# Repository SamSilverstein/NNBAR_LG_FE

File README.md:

# nnbar-calo-prototype

Readout electronics for NNBAR calorimeter prototype at SU
# NNBAR_LG_FE

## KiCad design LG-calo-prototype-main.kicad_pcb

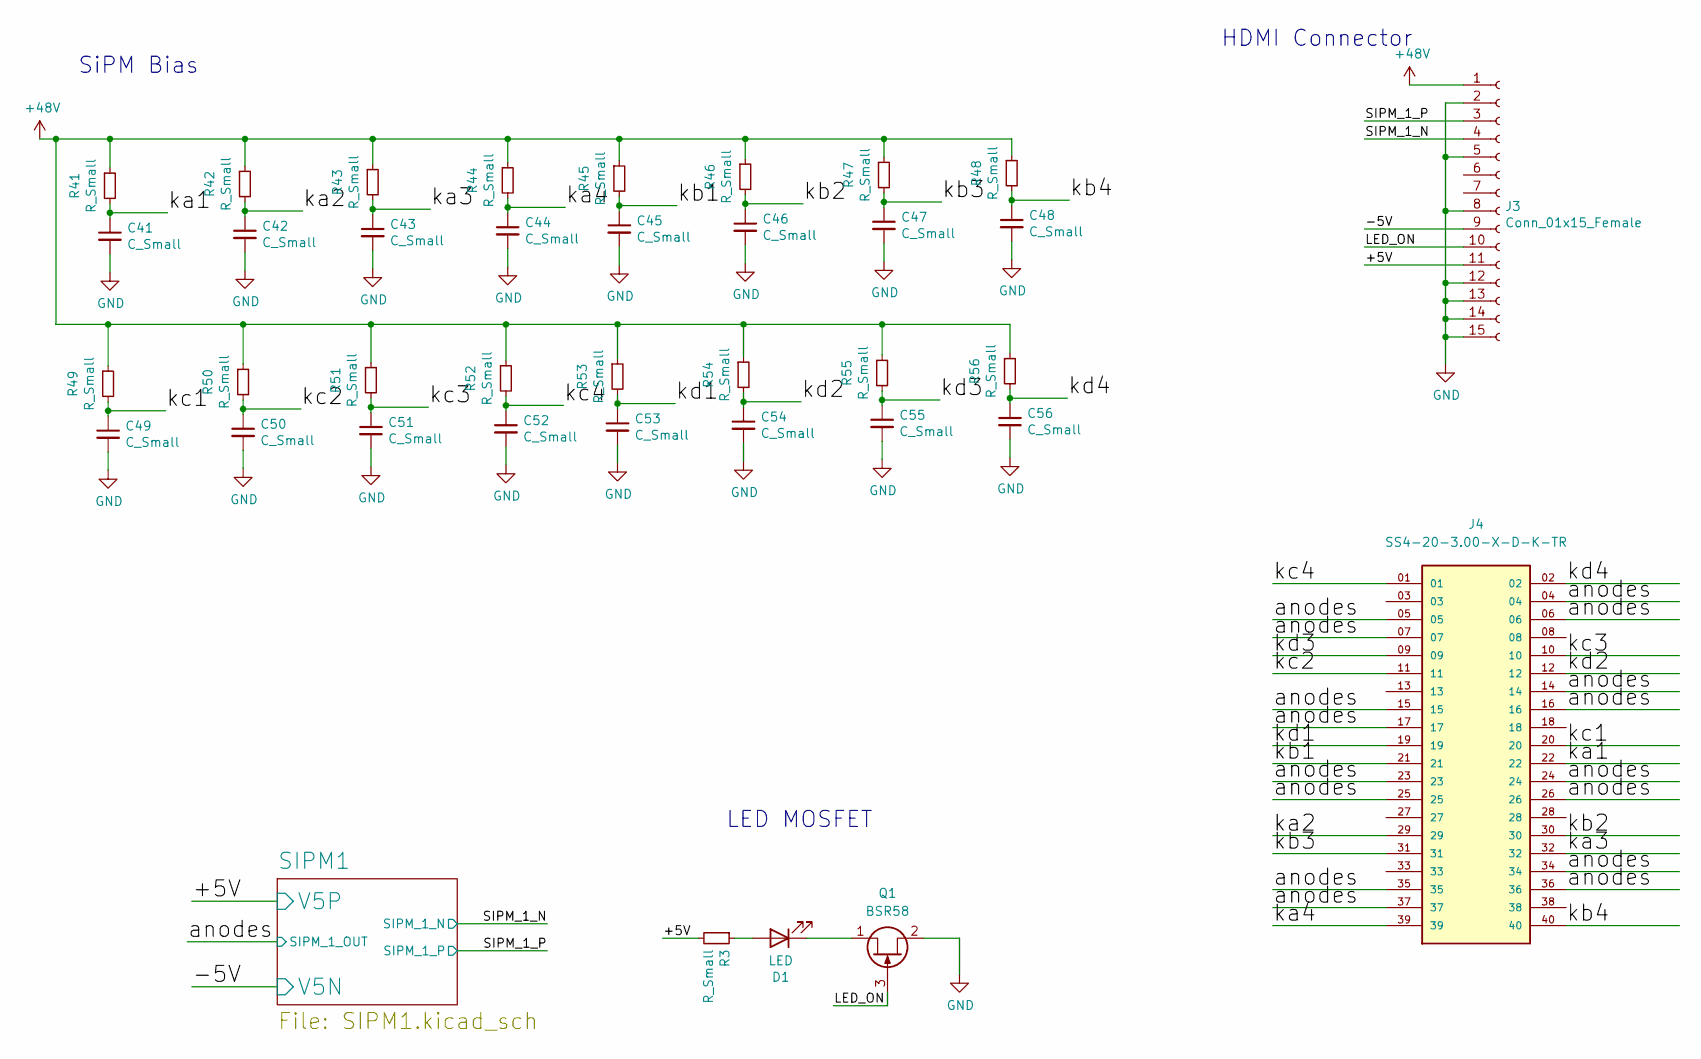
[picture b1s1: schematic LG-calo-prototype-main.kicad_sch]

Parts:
C41, C42, C43, C44, C45, C46, C47, C48, C49, C50, C51, C52, C53, C54, C55, C56: C_Small; C_0603_1608Metric
D1: LED; D_0603_1608Metric_Pad1.05x0.95mm_HandSolder
J3: Conn_01x15_Female; HDMI_Micro-D_Molex_46765-1x01
J4: SS4-20-3.00-X-D-K-TR; SAMTEC_SS4-20-3.00-X-D-K-TR; PARTREV K
Q1: BSR58; SOT-23
R3, R41, R42, R43, R44, R45, R46, R47, R48, R49, R50, R51, R52, R53, R54, R55, R56: R_Small; R_0603_1608Metric

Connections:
+48V: J3.1, R41.1, R42.1, R43.1, R44.1, R45.1, R46.1, R47.1, R48.1, R49.1, R50.1, R51.1, R52.1, R53.1, R54.1, R55.1, R56.1
/+5V: J3.11, R3.2; also elsewhere on the board
/-5V: J3.9; also elsewhere on the board
/LED_ON: J3.10, Q1.3 (G)
/SIPM_1_N: J3.4; also elsewhere on the board
/SIPM_1_P: J3.3; also elsewhere on the board
/anodes: J4.04, J4.05, J4.06, J4.07, J4.14, J4.15, J4.16, J4.17, J4.23, J4.24, J4.25, J4.26, J4.34, J4.35, J4.36, J4.37; also elsewhere on the board
/ka1: C41.1, J4.22, R41.2
/ka2: C42.1, J4.29, R42.2
/ka3: C43.1, J4.32, R43.2
/ka4: C44.1, J4.39, R44.2
/kb1: C45.1, J4.21, R45.2
/kb2: C46.1, J4.30, R46.2
/kb3: C47.1, J4.31, R47.2
/kb4: C48.1, J4.40, R48.2
/kc1: C49.1, J4.20, R49.2
/kc2: C50.1, J4.11, R50.2
/kc3: C51.1, J4.10, R51.2
/kc4: C52.1, J4.01, R52.2
/kd1: C53.1, J4.19, R53.2
/kd2: C54.1, J4.12, R54.2
/kd3: C55.1, J4.09, R55.2
/kd4: C56.1, J4.02, R56.2
GND: C41.2, C42.2, C43.2, C44.2, C45.2, C46.2, C47.2, C48.2, C49.2, C50.2, C51.2, C52.2, C53.2, C54.2, C55.2, C56.2, J3.2, J3.5, J3.8, J3.12, J3.13, J3.14, J3.15, Q1.2 (S); also elsewhere on the board
unnamed: D1.1 (K), Q1.1 (D)
unnamed: D1.2 (A), R3.1

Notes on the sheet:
HDMI Connector
LED MOSFET
SiPM Bias

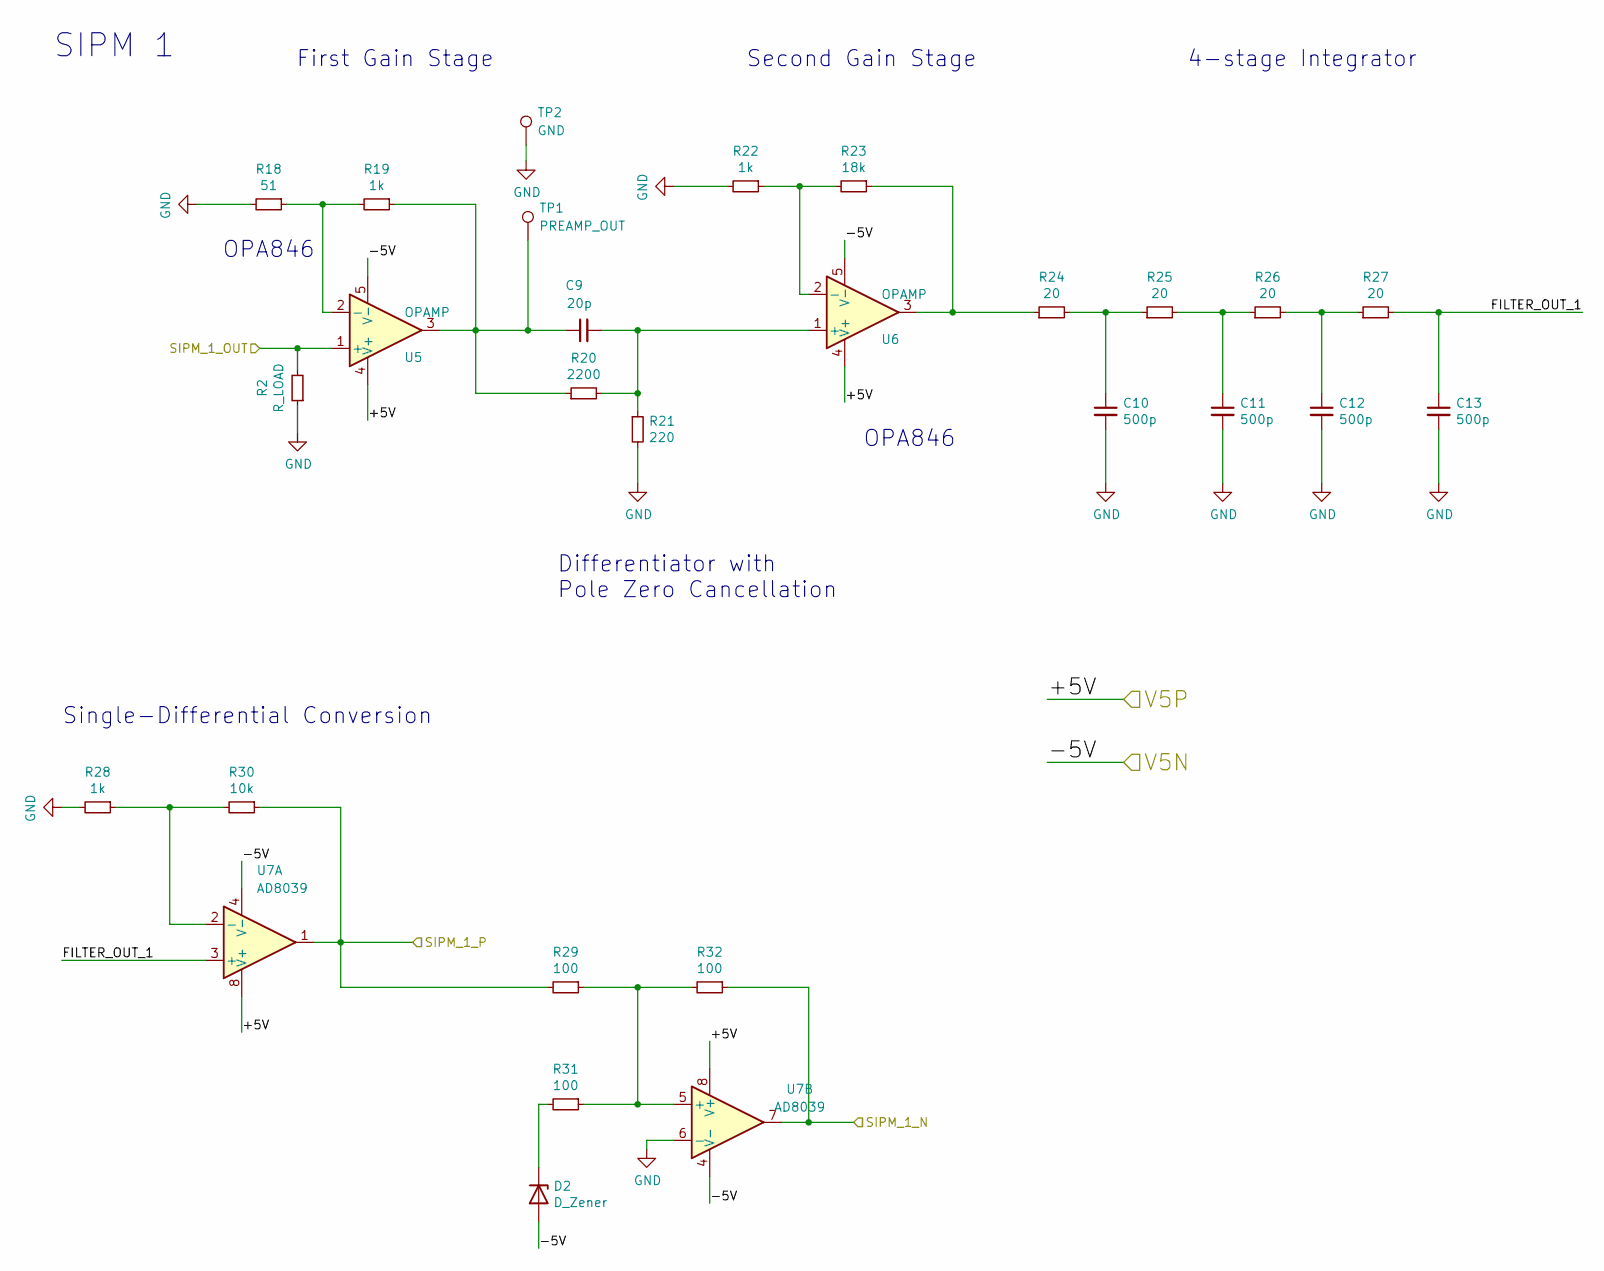
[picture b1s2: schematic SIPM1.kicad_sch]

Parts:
C9: 20p; C_0603_1608Metric
C10, C11, C12, C13: 500p; C_0603_1608Metric
D2: D_Zener; D_0603_1608Metric_Pad1.05x0.95mm_HandSolder
R2: R_LOAD; R_0603_1608Metric
R18: 51; R_0603_1608Metric
R19, R22, R28: 1k; R_0603_1608Metric
R20: 2200; R_0603_1608Metric
R21: 220; R_0603_1608Metric
R23: 18k; R_0603_1608Metric
R24, R25, R26, R27: 20; R_0603_1608Metric
R29, R31, R32: 100; R_0603_1608Metric
R30: 10k; R_0603_1608Metric
TP1: PREAMP_OUT; TestPoint_Pad_D2.0mm
TP2: GND; TestPoint_Pad_D2.0mm
U5, U6: OPAMP; OPA846
U7: AD8039; SOIC-8_3.9x4.9mm_P1.27mm

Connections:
/+5V: U5.4 (V+), U6.4 (V+), U7.8 (V+); also elsewhere on the board
/-5V: D2.2 (A), U5.5 (V-), U6.5 (V-), U7.4 (V-); also elsewhere on the board
/SIPM1/FILTER_OUT_1: C13.1, R27.2, U7.3 (+)
/SIPM_1_N: R32.1, U7.7; also elsewhere on the board
/SIPM_1_P: R29.2, R30.1, U7.1; also elsewhere on the board
/anodes: R2.2, U5.1 (+); also elsewhere on the board
GND: C10.2, C11.2, C12.2, C13.2, R2.1, R18.2, R21.2, R22.2, R28.2, TP2.1, U7.6 (-); also elsewhere on the board
unnamed: C9.1, R19.1, R20.1, TP1.1, U5.3
unnamed: C9.2, R20.2, R21.1, U6.1 (+)
unnamed: C10.1, R24.2, R25.1
unnamed: C11.1, R25.2, R26.1
unnamed: C12.1, R26.2, R27.1
unnamed: D2.1 (K), R31.2
unnamed: R18.1, R19.2, U5.2 (-)
unnamed: R22.1, R23.2, U6.2 (-)
unnamed: R23.1, R24.1, U6.3
unnamed: R28.1, R30.2, U7.2 (-)
unnamed: R29.1, R31.1, R32.2, U7.5 (+)

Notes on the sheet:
Single-Differential Conversion
Second Gain Stage
4-stage Integrator
Differentiator with Pole Zero Cancellation
First Gain Stage
SIPM 1
OPA846

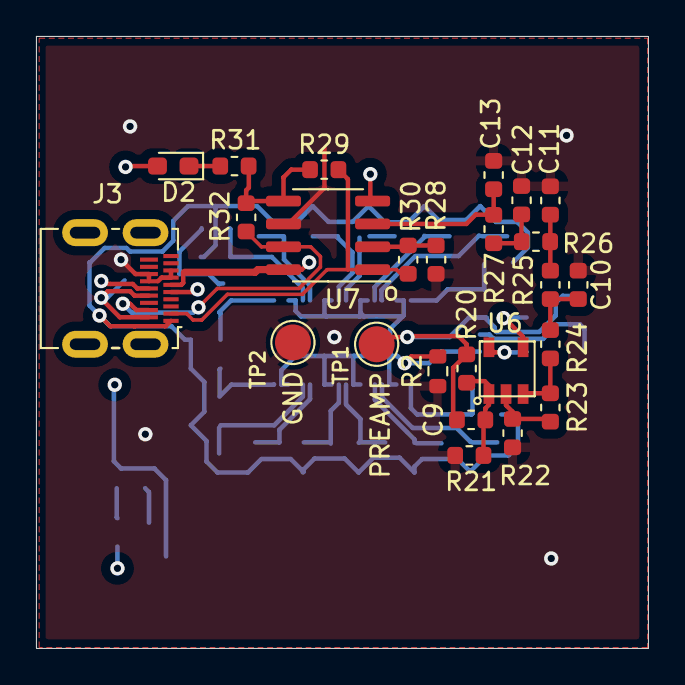
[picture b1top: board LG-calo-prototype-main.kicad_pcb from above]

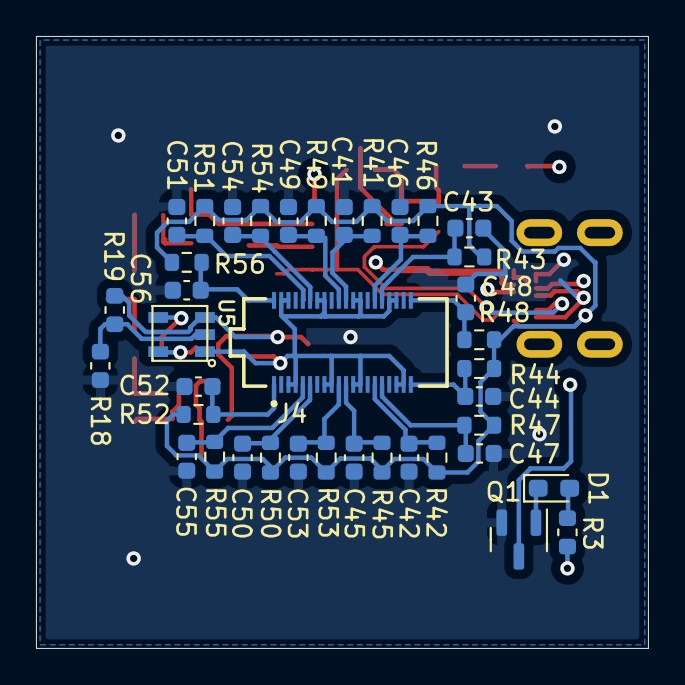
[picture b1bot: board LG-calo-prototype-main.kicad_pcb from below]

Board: 4 copper layers, 34.0 x 34.0 mm, 64 parts (39 on the bottom side), 38 nets.

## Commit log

2022-10-14 Add files via upload
    Initial upload of KICAD 6 versin
